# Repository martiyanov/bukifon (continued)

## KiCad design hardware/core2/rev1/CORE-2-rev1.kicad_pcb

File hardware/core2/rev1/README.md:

# CORE-2 rev.1 — PCB scaffold (PRE-FREEZE)

> **Не заказывать PCB.** Это каркас разводки из `mechanical/board-fit/`: контур, крепёж,
> keepout-зоны и стек. Нет посадочных мест компонентов (кроме крепежа), нет netlist/связей,
> нет меди/трасс. Следующий шаг — импорт схемы CORE-2 rev.3 (netlist) и посадочных мест.

## Что есть

| Файл | Что |
|---|---|
| `CORE-2-rev1.kicad_pcb` | плата: Edge.Cuts 200×108 мм, 4×M3 (Ø3.4, H1–H4), keepout-зоны, стек 6 слоёв 1.6 мм |
| `CORE-2-rev1.svg/.pdf` | контур + шелкография (для проверки/обсуждения) |
| `CORE-2-rev1.drc.rpt` | `kicad-cli pcb drc --severity-all`: **0 нарушений, 0 unconnected** |
| `gen_scaffold.py` | генератор из `mechanical/board-fit/board-spec.json` (общий для CORE/PANEL/PWR) |
| `verify_scaffold.py` | сверка координат с board-spec, допуск **±0.05 мм** — **PASS** |

## Параметры

- Контур: прямоугольник 200×108 мм (origin world 90;51), площадь 21 600 мм².
- Крепёж: 4×M3 Ø3.4 (NPTH, стойка Ø7) — H1 (5;8), H2 (195;8), H3 (5;100), H4 (195;100) в локальных мм.
- Стек: 6 меди (F.Cu / In1–In4 / B.Cu), FR4, 1.6 мм; толщина меди 0.035 мм (1 oz), диэлектрик распределён.
- Keepout (только медь/трассы/via, NPTH-пады разрешены): `C6-antenna` 40×20 + правило ≥15 мм,
  `analog` (DAC/ADC, звезда GND), `DC-DC` (тепловой/горячий контур).
  `USB-C` keepout из board-spec лежит вне контура платы (окно в задней стенке корпуса) — в плату не переносится.

## Проверки

- **DRC**: 0 errors / 0 warnings / 0 unconnected (`CORE-2-rev1.drc.rpt`).
- **Сверка с board-spec**: PASS (±0.05 мм): контур, 4 отверстия, толщина 1.6, 6 Cu, keepout-зоны.
- Импорт DXF (`mechanical/board-fit/core2.dxf`) в KiCad: File→Import→DXF→Edge.Cuts —
  альтернатива; текстовые сегменты сгенерированы точно по `board-spec.json` (DXF-круги
  крепежа заменены NPTH-падами, как требует DFM).

## Что дальше

1. Импорт netlist CORE-2 rev.3 (`hardware/core2/CORE-2.kicad_sch` → Update PCB) после снятия PRE-FREEZE.
2. Посадочные места (модуль P4, C6, FPC-40, IDC, аудио/джеки, TP-пады) + правила DRC.
3. Медная заливка/GND-полигоны, стек-ап импедансов (USB HS 90 Ω), keepout-механика (антенна vs H1).
4. DFM-ревью `hardware/core2/dfm.md` + `docs/38`, затем заказ прототипов 3–5 шт.

## Нетлист и посадочные места — первый импорт (2026-11-06)

- Источник: `hardware/core2/netlist.xml` (CORE-2 rev.3) + `BOM-core2.csv` (footprint по позициям).
- **Refs: 373/373** на плате; 4 NPTH-крепления (H1–H4) — из каркаса.
- **Footprints: 373** (имена из BOM; в PCB — bare-имена и упрощённые пады 0.5×0.8/шаг 1.0 с
  корректными номерами/числом; реальные `.kicad_mod` подтянуть при разводке). Pads: **1224**.
- **Placeholder: 16** — требуют реальных футпринтов до трассировки:
  `A1` (P4-модуль/адаптер), `U31` (C6-MINI-1), `U22` (BQ24074), `U26` (MP1584),
  `J6/J7/J8/J9/J10` (TRS/3.5 джеки), `J11` (audio jack), `J12` (DC jack), `J13` (mic TRS),
  `J20` (mic TRS), `SW1/SW2/SW3` (кнопки/тумблер).
- Зоны: `J1` USB-C у задней кромки, `U31` C6 — рядом с антенной (вне keepout), `A1` — центр;
  остальное — сетка по секциям (DC-DC/аналог — при ручной разводке).
- **DRC: 0 errors / 0 warnings; unconnected (неразведённые) = 499** — допустимо на этом этапе.
- Перегенерация: `python gen_scaffold.py && python import_netlist.py && python verify_import.py`
  (из корня репозитория пути уже учтены; скрипты лежат в `hardware/core2/rev1/`).
- Дальше: заменить 16 placeholder на реальные посадочные места, затем трассировка — после MCU freeze.

## Реальные футпринты и DRC-правила (2026-11-06)

- **Placeholder'ы заменены полностью (0):** A1 — custom `A1_P4_MODULE_ADAPTER` (2×32, шаг 2.54,
  габарит адаптера 90×28), U31 — custom `C6_MINI_1` (13.2×16.6), U26 — custom `MP1584_MODULE`
  (4 пада), U22 — `Package_DFN_QFN:QFN-16-1EP_3x3mm_P0.5mm_EP1.75x1.75mm`, J6–J11/J13/J20 —
  `Connector_Audio:Jack_3.5mm_CUI_SJ1-3535NG_Horizontal`, J12 — `Connector_BarrelJack:BarrelJack_CUI_PJ-063AH_Horizontal`,
  SW1–SW3 — `Button_Switch_THT:SW_PUSH_6mm`. Кастомные `.kicad_mod` — в `footprints/`
  (+`fp-lib-table`), вставлены через **pcbnew Python API** (реальная геометрия, пады с net).
- **Стандартные пассивные/IC**: footprint-имена из BOM (KiCad-библиотеки); в каркасе пады
  упрощённые (0.5×0.8/шаг 1.0) — полные `.kicad_mod` подтягиваются при разводке
  (`import_netlist.py`: generic-пады; `add_real_footprints.py`: реальные для заменённых).
- **Footprints: 373** (+4 NPTH), pads **1259**; refs 373/373; **DRC 0 errors / 0 warnings**,
  unconnected 499 (неразведённые).
- **DRC-правила/классы** (`CORE-2-rev1.kicad_pro`): `Default`, `Power` (+12/−12/5/3.3/VSYS…,
  ширина 1.0 мм), `USB_HS` (90 Ω: diff 0.2/0.2, clearance 0.15), `Audio` (0.25 мм),
  `RF` (C6 SPI); track widths 0.2–2.0, via 0.6/0.3 и 0.8/0.45, diff pair 0.2/0.2;
  правила-исключения для каркаса (silk/courtyard) — в `rule_severities`.
- **GND-полигоны (план, без заливки):** F.Cu/B.Cu GND-заливка после трассировки; аналоговая
  зона (DAC/ADC) — отдельный AGND-полигон, звезда в NT1/NT2; PGND — силовая зона, соединение
  в одной точке у J17; под антенной C6 — запрет меди (keepout 40×20 + ≥15 мм). Заливку делать
  только после MCU freeze/трассировки.

## Статус: реальные пассивы/GND-полигоны (2026-11-06)

- Placeholder'ы: **0** (A1/C6/MP1584/CHOC/джеки/кнопки/QFN — реальные).
- Стандартные пассивы: остаются **упрощёнными падами 0.5×0.8 (328)**; footprint-имена из BOM
  назначены. Полный перевод (`build_full_pcb.py`, реальные `.kicad_mod` для всех) пока **не прошёл
  DRC**: крупные реальные футпринты не упаковываются без пересечений на 200×108 — требуется
  трассировка/оптимизация размещения после MCU freeze.
- GND/AGND/PGND-полигоны: **не залиты** (план в docs/82 §11; `add_gnd_zones.py` даёт
  `isolated_copper`/`zones_intersect`/`starved_thermal`) — следующий шаг вместе с трассировкой.
- Текущий DRC: **0 errors / 0 warnings**; `verify_import.py` PASS (+счётчик `SIMPLIFIED PADS: 328`).

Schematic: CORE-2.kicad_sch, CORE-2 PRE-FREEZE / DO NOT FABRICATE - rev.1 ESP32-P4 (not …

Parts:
A1: ESP32-P4NRW32 + 32MB PSRAM (module TBD)
C1, C4, C6, C17, C20, C32, C41, C48, C49, C57, C63, C82, C84, C94: 10uF/10V; C_0805_2012Metric
C2: 100nF/16V; C_0805_2012Metric
C3, C5, C7, C19, C21, C22, C26, C37, C42, C43, C44, C45, C46, C47, C51, C54, C55, C56, C60, C61, C62, C64, C65, C68, C69, C73, C75, C76, C81, C83, C85, C86, C87, C88, C89, C90, C91, C92, C93, C95, C96, C97, C98, C101, C102, C103, C115, C116, C118, C119, C120, C121, C127, C129: 100nF; C_0805_2012Metric
C8, C16, C99, C100: 100nF; C_0805_2012Metric; not fitted
C9, C13: 100pF; C_0805_2012Metric; not fitted
C10, C14: 10uF/10V; C_0805_2012Metric; not fitted
C11, C28: 220uF/25V; CP_Elec_6.3x7.7; not fitted
C12, C29: 100nF/50V; C_0805_2012Metric; not fitted
C15: 220uF/10V; CP_Elec_6.3x7.7; not fitted
C18, C40, C114, C117: 100uF/10V; CP_Elec_6.3x7.7
C24, C25, C35: 1uF; C_0805_2012Metric
C27: 1.5nF; C_0805_2012Metric; not fitted
C30: 100uF/25V; CP_Elec_6.3x7.7; not fitted
C31, C70, C71, C77, C79: 100pF; C_0805_2012Metric
C33: 10uF/35V; C_0805_2012Metric
C34, C104, C106, C107, C109, C111, C113: 100nF/50V; C_0805_2012Metric
C36, C53: 22uF/10V; C_0805_2012Metric
C38, C110, C112: 100uF/25V; CP_Elec_6.3x7.7
C39: 220uF/25V; CP_Elec_6.3x7.7
C58, C122: 1uF/10V; C_0805_2012Metric
C59: 1uF/10V; CP_Elec_6.3x7.7
C66, C67: 10uF/16V; CP_Elec_6.3x7.7
C72, C74, C128: 10uF/10V; CP_Elec_6.3x7.7
C78, C80, C126: 1uF/16V; C_0805_2012Metric
C105, C108: 10uF/25V; CP_Elec_6.3x7.7
C123, C125: 470nF; C_0805_2012Metric
C124: 2.2uF/10V; C_0805_2012Metric
D1, D30: SMAJ5.0A; D_SMA
D2, D7, D18, D19, D21, D22, D28: SS34; D_SMA
D3: CHG; C_0805_2012Metric
D4, D5, D6: SS34; D_SMA; not fitted
D8, D9, D10, D11, D12, D13, D14, D15, D16, D17, D24, D25: BAT54S; SOT-23
D20, D23, D29: SMAJ15A; D_SMA
D31: MIC ON; C_0805_2012Metric
F1: 1.5A; Fuse_1206_3216Metric
F2, F4: 0.5A; Fuse_1206_3216Metric
F3, F5: 0.3A; Fuse_1206_3216Metric
FB1, FB2, FB3, FB4, FB5, FB6, FB7, FB8: 600R@100MHz; L_0805_2012Metric
J1: USB-C 16P (data+charge); USB_C_Receptacle_HRO_TYPE-C-31-M-12
J2: BATTERY 1S2P; JST_XH_B2B-XH-A_1x02_P2.50mm_Vertical; not fitted
J4: UART0 TP; PinHeader_1x03_P2.54mm_Vertical
J5: microSD (SDIO 1-bit); microSD_HC_Hirose_DM3AT-SF-PEJM5
J6: MIDI IN TRS-A
J7: MIDI OUT TRS-A
J8: LINE OUT L/R 3.5mm
J9: PHONES 3.5mm
J10: AUDIO IN L 3.5mm
J11: AUDIO IN R 3.5mm
J12: DC 12V 5.5/2.1
J13: EXPRESSION TRS; not fitted
J14: PANEL-2 J14 (IDC-26) analog field [rev.2 canon]; IDC-Header_2x13_P2.54mm_Latch12.0mm_Vertical
J15: PANEL-2 J12 (FFC-40) LCD RGB565+BL [rev.2 canon]; Hirose_FH12-40S-0.5SH_1x40-1MP_P0.50mm_Horizontal
J16: PANEL-2 J13 (IDC-16) digital/power [rev.2 canon]; IDC-Header_2x08_P2.54mm_Latch6.5mm_Vertical
J17: PWR-2 J3 (IDC-20) [rev.2]; IDC-Header_2x10_P2.54mm_Vertical
J18: PWR-2 J4 (IDC-12) [rev.2]; IDC-Header_2x06_P2.54mm_Vertical
J19: PANEL-2 MEMS mic (IDC-6); IDC-Header_2x03_P2.54mm_Vertical
J20: MIC IN 3.5mm TRS (electret)
L1, L2: 22uH; L_1210_3225Metric; not fitted
L3: 220uH; L_1210_3225Metric; not fitted
L4: 22uH; L_1210_3225Metric
NT1: AGND=DGND; NetTie-2_SMD_Pad0.5mm
NT2: DGND=PGND; NetTie-2_SMD_Pad0.5mm
P1: PicoMod analog bus IDC-26 PORT1; IDC-Header_2x13_P2.54mm_Latch12.0mm_Vertical
P2: PicoMod analog bus IDC-26 PORT2; IDC-Header_2x13_P2.54mm_Latch12.0mm_Vertical
Q1, Q2: AO3400A; SOT-23; not fitted
Q3, Q4, Q5: 2N7000; TO-92_Inline
R1, R2: 1.5k; R_0805_2012Metric
R3: 2k; R_0805_2012Metric
R4, R19, R20, R37, R38, R63, R65, R75, R85, R88, R92, R93, R99, R100, R108, R110, R113: 100k; R_0805_2012Metric
R5, R14: 10k; R_0805_2012Metric; not fitted
R6, R43, R44, R57, R58, R59, R60, R61, R62, R67, R68, R71, R72, R84, R87, R103, R104, R114: 1k; R_0805_2012Metric
R7, R90: 330; R_0805_2012Metric; not fitted
R10: 91k; R_0805_2012Metric; not fitted
R11: 4.7k; R_0805_2012Metric; not fitted
R12, R15: 100k; R_0805_2012Metric; not fitted
R13: 75k; R_0805_2012Metric; not fitted
R16: 0.33; R_0805_2012Metric; not fitted
R17: 33k; R_0805_2012Metric; not fitted
R18: 3.9k; R_0805_2012Metric; not fitted
R21: 3.09k; R_0805_2012Metric
R22, R23, R24, R27, R30, R31, R35, R36, R51, R52, R53, R54, R55, R56, R77, R91: 10k; R_0805_2012Metric
R28, R29: 5.1k; R_0805_2012Metric
R39, R40, R41, R42: 100; R_0805_2012Metric
R45, R46, R47, R48, R49, R50: 39k; R_0805_2012Metric
R64, R66, R101, R102: 16.5k; R_0805_2012Metric
R69, R70, R76: 47k; R_0805_2012Metric
R73, R74: 1k; R_0805_2012Metric; not fitted
R78, R79, R106: 2.2k; R_0805_2012Metric
R80, R83: 220; R_0805_2012Metric
R81, R86, R89: 4.7k; R_0805_2012Metric
R82: 33; R_0805_2012Metric
R94, R95, R96, R97, R98, R105: 0R; R_0805_2012Metric
R107: 150k; R_0805_2012Metric
SW1: BOOT
SW2: RESET
SW3: MIC MUTE
TB1: Rear audio terminal block; TerminalBlock_Phoenix_MKDS-1-12-3.81_1x12_P3.81mm_Horizontal
TB2: Rear MIDI/DC/EXPR terminal block; TerminalBlock_Phoenix_MKDS-1-10-3.81_1x10_P3.81mm_Horizontal; not fitted
TH1: NTC 10k; R_0805_2012Metric; not fitted
TH2: NTC 10k; R_0805_2012Metric
TP1: VBUS_CHG; TestPoint_Pad_D1.5mm
TP2: VSYS; TestPoint_Pad_D1.5mm
TP3: 12V; TestPoint_Pad_D1.5mm
TP4: -12V; TestPoint_Pad_D1.5mm
TP5: 5V; TestPoint_Pad_D1.5mm
TP6: 3V3; TestPoint_Pad_D1.5mm
TP7: 3V3_MCU; TestPoint_Pad_D1.5mm
TP8: BATT_MON; TestPoint_Pad_D1.5mm
TP9: I2S_MCLK; TestPoint_Pad_D1.5mm
TP10: SD_CLK; TestPoint_Pad_D1.5mm
TP11: USB_HS_DP; TestPoint_Pad_D1.5mm
TP12: USB_HS_DM; TestPoint_Pad_D1.5mm
TP13: AGND; TestPoint_Pad_D1.5mm
TP14: DGND; TestPoint_Pad_D1.5mm
TP15: PGND; TestPoint_Pad_D1.5mm
TP16: LED_DATA; TestPoint_Pad_D1.5mm
TP17: CHIP_PU; TestPoint_Pad_D1.5mm
TP18: BOOT; TestPoint_Pad_D1.5mm
TP19: 3V3_C6; TestPoint_Pad_D1.5mm
TP20: BL_20V; TestPoint_Pad_D1.5mm
TP21: C6_CS; TestPoint_Pad_D1.5mm
TP22: C6_RST; TestPoint_Pad_D1.5mm
TP23: N12_EXT; TestPoint_Pad_D1.5mm
TP24: 5V_EXT; TestPoint_Pad_D1.5mm
TP25: 5V_LED; TestPoint_Pad_D1.5mm
TP26: PWR_GOOD; TestPoint_Pad_D1.5mm
TP27: EN_RAILS; TestPoint_Pad_D1.5mm
TP28: LED_RET; TestPoint_Pad_D1.5mm
TP29: I2S_BCK; TestPoint_Pad_D1.5mm
TP30: I2S_LRCK; TestPoint_Pad_D1.5mm
TP31: MIC_DATA; TestPoint_Pad_D1.5mm
TP32: MIC_BCK; TestPoint_Pad_D1.5mm
U20, U48, U49: USBLC6-2SC6; SOT-23-6
U22: BQ24074RGT
U23: BQ29700DSER; SOT-23-6; not fitted
U24: MT3608 (+12V); SOT-23-6; not fitted
U25: MT3608 (+5V); SOT-23-6; not fitted
U26: MP1584 3.3V/3A (MCU)
U27: AP2112K-3.3; SOT-23-5
U28: MC34063; DIP-8_W7.62mm; not fitted
U29: MT3608 (+20V BL); SOT-23-6
U30: AP2112K-3.3 (C6); SOT-23-5
U31: ESP32-C6-MINI-1 (Wi-Fi6/BLE5.3)
U32: PCM5102A; TSSOP-20_4.4x6.5mm_P0.65mm
U33: TL072; DIP-8_W7.62mm
U34: PCM1808PWR; TSSOP-14_4.4x5mm_P0.65mm
U35: MCP4728A0-E/UN (0x60); MSOP-10_3x3mm_P0.5mm
U36: MCP4728A1-E/UN (0x61); MSOP-10_3x3mm_P0.5mm
U37, U38, U39, U45: TL074; DIP-14_W7.62mm
U40: MCP3208; DIP-16_W7.62mm
U41: 24LC32A; DIP-8_W7.62mm
U42: 6N137; DIP-8_W7.62mm
U43: 74HCT125; SOIC-14_3.9x8.7mm_P1.27mm
U44: 74HCT1G125; SOT-353_SC-70-5; not fitted
U46: MAX9814 (AGC mic amp); TDFN-14-1EP_3x3mm_P0.4mm_EP1.78x2.35mm
U47: TS5A23157 (line/mic switch); MSOP-10-1EP_3x3mm_P0.5mm_EP1.68x1.88mm

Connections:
3V3: C25.1, C26.1, C56.1, C57.1, C61.1, C62.1, C63.1, C64.1, C76.1, C81.1, C82.1, C83.1, C84.1, C96.1, C103.1, D16.2 (K), D17.2 (K), D24.2 (K), D25.2 (K), FB5.1, FB6.1, FB8.1, J5.4 (VDD), J13.R, R30.1, R31.1, R35.1, R36.1, R69.1, R78.1, R79.1, R81.1, R91.1, R92.1, R93.1, R105.2, TB2.10, TH2.1, TP6.1, U27.5 (VOUT), U32.1 (CPVDD), U32.8 (AVDD), U32.20 (DVDD), U34.4 (VDD), U35.1 (VDD), U36.1 (VDD), U40.16 (Vdd), U41.1 (A0), U41.2 (A1), U41.3 (A2), U41.8 (VCC), U47.8 (VCC), U48.5 (VBUS), U49.5 (VBUS)
3V3_C6: C36.1, C37.1, C53.1, C54.1, C55.1, R27.1, TP19.1, U30.5 (VOUT), U31.1 (3V3)
3V3_MCU: A1.3 (3V3), A1.4 (3V3), C20.1, C21.1, C22.1, C42.1, C43.1, C44.1, C45.1, C46.1, C47.1, C48.1, C49.1, FB1.2, R22.1, R23.1, R24.2, TP7.1
3V3_MCU_RAW: C18.1, C19.1, FB1.1, U26.3 (OUT+)
3V3_MIC: C128.1, C129.1, FB8.2, J19.6, R113.1, R114.1, U46.5 (VDD)
3V3_PANEL: C41.1, FB5.2, J15.27, J15.28, J16.11
5V: C13.1, C15.1, C16.1, C17.1, C24.1, C32.1, C35.1, C74.1, C75.1, C117.1, D5.2 (A), D8.2 (K), D9.2 (K), FB4.1, FB7.2, L4.1, R13.1, R19.1, R83.1, R86.1, R89.1, TP5.1, U26.1 (IN+), U27.1 (VIN), U27.3 (EN), U29.5 (IN), U30.1 (VIN), U30.3 (EN), U34.3 (VCC), U42.7 (EN), U42.8 (VCC), U43.4 (2OE), U43.10 (3OE), U43.13 (4OE), U43.14 (VCC), U44.5 (VCC)
5V_EXT: C114.1, C115.1, FB7.1, J17.13, J17.14, TP24.1
5V_LED: C116.1, J16.9, J16.13, J17.17, TP25.1
5V_PANEL: C40.1, FB4.2
12V: C9.1, C11.1, C12.1, C29.1, C30.1, C68.1, C85.1, C87.1, C92.1, C120.1, D2.2 (A), D4.2 (A), D10.2 (K), D11.2 (K), D12.2 (K), D13.2 (K), D14.2 (K), D15.2 (K), FB2.1, R10.1, R16.1, TP3.1, U28.6 (Vin), U33.8 (V+), U37.4 (V+), U38.4 (V+), U39.4 (V+), U45.4 (V+)
12V_B: C38.1, D18.2 (A), D21.2 (A), F2.1, F4.1, FB2.2
12V_EXT: C110.1, C111.1, D2.1 (K), J12.1, J17.5, J17.6, TB2.7
12V_P1: C104.1, C105.1, D18.1 (K), D29.1 (A1), F2.2, P1.1
12V_P2: C107.1, C108.1, D21.1 (K), D23.1 (A1), F4.2, P2.1
-12V: C27.2, C28.2, C29.2, C69.1, C86.1, C88.1, C93.1, C121.1, D19.1 (K), FB3.1, L3.2, R18.2, TP4.1, U28.4 (GND), U33.4 (V-), U37.11 (V-), U38.11 (V-), U39.11 (V-), U45.11 (V-)
-12V_B: C39.2, D22.1 (K), D28.1 (K), F3.1, F5.1, FB3.2
AGND: C59.1, C60.2, C61.2, C63.2, C64.2, C65.2, C68.2, C69.2, C70.2, C71.2, C72.2, C73.2, C74.2, C75.2, C77.2, C79.2, C81.2, C82.2, C83.2, C84.2, C85.2, C86.2, C87.2, C88.2, C89.2, C90.2, C91.2, C92.2, C93.2, C94.2, C95.2, C96.2, C97.2, C98.2, C99.2, C100.2, C101.2, C102.2, C118.2, C119.2, C120.2, C121.2, C122.2, C123.2, C124.2, C125.2, C128.2, C129.2, D8.1 (A), D9.1 (A), D10.1 (A), D11.1 (A), D12.1 (A), D13.1 (A), D14.1 (A), D15.1 (A), D16.1 (A), D17.1 (A), D24.1 (A), D25.1 (A), D30.2 (A2), J8.S, J9.S, J10.S, J11.S, J13.S, J14.2, J14.4, J14.6, J14.8, J14.10, J14.12, J14.14, J14.16, J14.18, J14.20, J14.22, J14.24, J14.26, J20.S, NT1.1, P1.6, P1.8, P1.10, P1.12, P1.18, P1.20, P1.22, P1.24, P2.6, P2.8, P2.10, P2.12, P2.18, P2.20, P2.22, P2.24, Q5.3 (S), R37.2, R38.2, R51.2, R52.2, R53.2, R54.2, R55.2, R56.2, R70.2, R74.2, R76.2, R77.2, R108.2, R110.2, SW3.2 (B), TB1.3, TB1.6, TB1.9, TB1.10, TB1.11, TB1.12, TP13.1, U32.3 (CPGND), U32.9 (AGND), U34.2 (AGND), U35.10 (VSS), U36.10 (VSS), U38.10 (+), U38.12 (+), U39.12 (+), U40.14 (AGND), U45.10 (+), U45.12 (+), U46.4 (NC4), U46.7 (GND), U46.9 (AR), U46.10 (GAIN), U46.11 (NC11), U46.15 (EP), U47.3 (GND)
AUDIN_L: J10.T, P1.17, P2.17, R43.1, TB1.7
AUDIN_L_C: C78.2, U34.13 (VINL)
AUDIN_L_F: C77.1, D8.3 (COM), R43.2, U47.9 (NC1)
AUDIN_R: J11.T, P1.19, P2.19, R44.1, TB1.8
AUDIN_R_C: C80.2, U34.14 (VINR)
AUDIN_R_F: C79.1, D9.3 (COM), R44.2, U47.7 (NC2)
AUDL_BUF: R39.1, R41.1, U33.1, U33.2 (-)
AUDOUT_L: C70.1, J8.T, P1.21, P2.21, R39.2, TB1.1
AUDOUT_R: C71.1, J8.R, P1.23, P2.23, R40.2, TB1.2
AUDR_BUF: R40.1, R42.1, U33.6 (-), U33.7
AUD_L_IN: C66.2, R37.1, U33.3 (+)
AUD_R_IN: C67.2, R38.1, U33.5 (+)
BATT_MON: C101.1, R75.2, R76.1, TP8.1, U40.7 (CH6)
BATT_MON_RAW: J18.1, R75.1
BATT_N: C8.2, J2.2, Q1.3 (S), U23.4 (VSS)
BATT_P: C6.1, C7.1, J2.1, J17.3, J17.4, R7.1, U22.2 (BAT), U22.3 (BAT)
BIAS: C123.1, U46.12 (BIAS)
BL_20V: C31.1, C33.1, C34.1, D7.2 (A), J15.31, R20.1, TP20.1
BL_CATHODE: J15.32, R97.1
BL_PWM: A1.16 (IO49), J15.30
BMS_MID: Q1.2 (D), Q2.2 (D)
BOOT: A1.8 (IO35), R22.2, SW1.1, TP18.1
BQ_BAT: C8.1, R7.2, U23.5 (BAT)
C6_CS: A1.10 (IO26), TP21.1, U31.7 (SPI_CS)
C6_DR: A1.12 (IO25), U31.9 (DATA_READY)
C6_HS: A1.11 (IO24), U31.8 (HANDSHAKE)
C6_RST: A1.13 (IO27), R27.2, TP22.1, U31.3 (EN)
CC1: J1.A5 (CC1), R28.1
CC2: J1.B5 (CC2), R29.1
CG: C124.1, U46.3 (CG)
CHG: D3.1 (K), U22.9 (~CHG)
CHG_LED: D3.2 (A), R6.2
CHIP_PU: A1.5 (EN), C51.1, R23.2, SW2.1, TP17.1
CP_M: C58.2, U32.4 (CAPM)
CP_P: C58.1, U32.2 (CAPP)
CT: C125.1, U46.1 (CT)
CVIN1: J14.9, R63.1
CVIN1_ADC: C89.1, D16.3 (COM), R67.2, U40.1 (CH0)
CVIN1_N: R63.2, R64.1, U39.2 (-)
CVIN1_RAW: R64.2, R67.1, U39.1
CVIN2: J14.11, R65.1
CVIN2_ADC: C90.1, D17.3 (COM), R68.2, U40.2 (CH1)
CVIN2_N: R65.2, R66.1, U39.6 (-)
CVIN2_RAW: R66.2, R68.1, U39.7
CVIN3: J14.13, R99.1
CVIN3_ADC: C118.1, D24.3 (COM), R103.2, U40.5 (CH4)
CVIN3_N: R99.2, R101.1, U45.2 (-)
CVIN3_RAW: R101.2, R103.1, U45.1
CVIN4: J14.15, R100.1
CVIN4_ADC: C119.1, D25.3 (COM), R104.2, U40.6 (CH5)
CVIN4_N: R100.2, R102.1, U45.6 (-)
CVIN4_RAW: R102.2, R104.1, U45.7
CVOUT1: D10.3 (COM), J14.1, P1.5, P2.5, R57.2
CVOUT2: D11.3 (COM), J14.3, P1.7, P2.7, R58.2
CVOUT3: D12.3 (COM), J14.5, P1.9, P2.9, R59.2
CVOUT4: D13.3 (COM), J14.7, P1.11, P2.11, R60.2
CVOUT5: D14.3 (COM), R61.2
CVOUT6: D15.3 (COM), R62.2
CVR0: R45.2, R57.1, U37.1
CVR1: R46.2, R58.1, U37.7
CVR2: R47.2, R59.1, U37.8
CVR3: R48.2, R60.1, U37.14
CVR4: R49.2, R61.1, U38.1
CVR5: R50.2, R62.1, U38.7
CVREF: C91.1, R69.2, R70.1, U39.10 (+)
CVREF_B: U39.3 (+), U39.5 (+), U39.8, U39.9 (-), U45.3 (+), U45.5 (+)
CVS0: R45.1, R51.1, U37.2 (-)
CVS1: R46.1, R52.1, U37.6 (-)
CVS2: R47.1, R53.1, U37.9 (-)
CVS3: R48.1, R54.1, U37.13 (-)
CVS4: R49.1, R55.1, U38.2 (-)
CVS5: R50.1, R56.1, U38.6 (-)
DAC_A: U35.6 (VOUTA), U37.3 (+)
DAC_B: U35.7 (VOUTB), U37.5 (+)
DAC_C: U35.8 (VOUTC), U37.10 (+)
DAC_D: U35.9 (VOUTD), U37.12 (+)
DAC_E: U36.6 (VOUTA), U38.3 (+)
DAC_F: U36.7 (VOUTB), U38.5 (+)
DAC_L: C66.1, U32.6 (OUTL)
DAC_R: C67.1, U32.7 (OUTR)
DGND: A1.1 (GND), A1.2 (GND), A1.63 (GND), A1.64 (GND), C20.2, C21.2, C22.2, C24.2, C25.2, C26.2, C35.2, C36.2, C37.2, C41.2, C42.2, C43.2, C44.2, C45.2, C46.2, C47.2, C48.2, C49.2, C51.2, C53.2, C54.2, C55.2, C56.2, C57.2, C62.2, C76.2, C103.2, J1.A1 (GND), J1.A12 (GND), J1.B1 (GND), J1.B12 (GND), J1.SH (SHIELD), J4.1, J5.6 (VSS), J5.SH (SHIELD), J6.S, J7.S, J15.1, J15.2, J15.19, J15.20, J15.25, J15.26, J15.29, J15.33, J15.34, J15.35, J15.36, J15.37, J15.38, J15.39, J15.40, J16.2, J16.4, J16.6, J16.8, J16.10, J16.12, J16.14, J19.2, J19.4, NT1.2, NT2.1, P1.14, P1.16, P2.14, P2.16, Q3.1 (S), Q4.1 (S), R28.2, R29.2, R85.2, R88.2, SW1.2, SW2.2, TB2.3, TB2.6, TP14.1, U20.2 (GND), U27.2 (GND), U30.2 (GND), U31.2 (GND), U31.10 (GND), U32.10 (DEMP), U32.11 (FLT), U32.16 (FMT), U32.19 (DGND), U34.5 (DGND), U34.10 (MD0), U34.11 (MD1), U34.12 (FMT), U35.4 (~LDAC), U36.4 (~LDAC), U40.9 (DGND), U41.4 (GND), U41.7 (WP), U42.5 (GND), U43.1 (1OE), U43.5 (2A), U43.7 (GND), U43.9 (3A), U43.12 (4A), U44.1 (~OE), U44.3 (GND), U48.2 (GND), U49.2 (GND)
EN5: R15.2, U25.4 (EN)
EN12: R12.2, U24.4 (EN)
ENBL: R19.2, U29.4 (EN)
EN_5V: J18.10, R96.2
EN_BUS12: J18.7, R94.2
EN_LED5: J14.25, J18.9
EN_N12: J18.8, R95.2
EN_RAILS: J16.15, R94.1, R95.1, R96.1, TP27.1
EXPR: J13.T, R73.1, TB2.9
EXPR_ADC: C99.1, R73.2
FADER1: J14.21, R71.1
FADER1_ADC: C97.1, R71.2, U40.3 (CH2)
FADER2: J14.23, R72.1
FADER2_ADC: C98.1, R72.2, U40.4 (CH3)
FB5: C13.2, R13.2, R14.1, U25.3 (FB)
FB12: C9.2, R10.2, R11.1, U24.3 (FB)
FBBL: C31.2, R20.2, R21.1, U29.3 (FB)
FUEL_ALRT: J18.5, R93.2
G1: Q3.2 (G), R84.2, R85.1
G2: Q4.2 (G), R87.2, R88.1
GATE1: J14.17, P1.13, P2.13, Q3.3 (D), R86.2
GATE1_GPIO: A1.19 (IO52), R84.1
GATE2: P1.15, P2.15, Q4.3 (D), R89.2
GATE2_GPIO: A1.20 (IO53), R87.1
G_BMS_C: Q1.1 (G), U23.2 (Cout)
G_BMS_D: Q2.1 (G), U23.3 (Dout)
I2C0_SCL: A1.36 (IO22), J16.3, J18.4, R79.2, U35.2 (SCL), U36.2 (SCL), U41.6 (SCL)
I2C0_SDA: A1.35 (IO21), J16.1, J18.3, R78.2, U35.3 (SDA), U36.3 (SDA), U41.5 (SDA)
I2S_ADC_DOUT: A1.34 (IO19), U34.9 (DOUT)
I2S_BCK: A1.31 (IO16), TP29.1, U32.13 (BCK), U34.8 (BCK)
I2S_DAC_DIN: A1.33 (IO18), U32.14 (DIN)
I2S_LRCK: A1.32 (IO17), TP30.1, U32.15 (LRCK), U34.7 (LRCK)
I2S_MCLK: A1.30 (IO20), TP9.1, U32.12 (SCK), U34.6 (SCKI)
ILIM: R1.1, U22.12 (ILIM)
ISET: R2.1, U22.16 (ISET)
ITERM: R3.1, U22.15 (ITERM)
LCD_B0: A1.47 (IO0), J15.14
LCD_B1: A1.48 (IO1), J15.15
LCD_B2: A1.49 (IO2), J15.16
LCD_B3: A1.50 (IO3), J15.17
LCD_B4: A1.51 (IO4), J15.18
LCD_DE: A1.44 (IO13), J15.22
LCD_DISP: A1.17 (IO50), R105.1
LCD_G0: A1.52 (IO5), J15.8
LCD_G1: A1.53 (IO23), J15.9
LCD_G2: A1.54 (IO28), J15.10
LCD_G3: A1.55 (IO29), J15.11
LCD_G4: A1.56 (IO30), J15.12
LCD_G5: A1.57 (IO31), J15.13
LCD_HSYNC: A1.45 (IO14), J15.23
LCD_PCLK: A1.43 (IO12), J15.21
LCD_R0: A1.58 (IO32), J15.3
LCD_R1: A1.59 (IO33), J15.4
LCD_R2: A1.60 (IO34), J15.5
LCD_R3: A1.61 (IO46), J15.6
LCD_R4: A1.62 (IO47), J15.7
LCD_VSYNC: A1.46 (IO15), J15.24
LDOO: C60.1, U32.18 (LDOO)
LED_5V: R90.1, U44.4 (Y)
LED_DATA: J16.7, R90.2, R98.2, TP16.1
LED_GPIO: A1.15 (IO48), R98.1, U44.2 (A)
LED_RET: J16.16, J17.18, TP28.1
MCP3208_CS: A1.40 (IO9), U40.10 (~CS/SHDN)
MC_A: R16.2, U28.1 (SwC), U28.7 (Ipk), U28.8 (DC)
MC_FB: R17.2, R18.1, U28.5 (Vfb)
MC_SW: D6.1 (K), L3.1, U28.2 (SwE)
MC_TC: C27.1, U28.3 (TC)
MICBIAS_N: C122.1, R106.1, R107.1, U46.13 (MCBIAS)
MICIN_A: C127.2, U46.8 (MICIN)
MIC_AGC: C126.1, U46.6 (MICOUT)
MIC_BCK: A1.24 (IO40), J19.1, TP32.1, U48.1 (I/O1), U48.6 (I/O1)
MIC_BIAS: J20.R, R106.2
MIC_DATA: A1.26 (IO42), J19.5, TP31.1, U49.1 (I/O1), U49.6 (I/O1)
MIC_IN: C127.1, D30.1 (A1), J20.T
MIC_LED_A: D31.2 (A), R114.2
MIC_LED_K: D31.1 (K), Q5.2 (D)
MIC_SEL: A1.14 (IO54), R110.1, U47.1 (IN1), U47.5 (IN2)
MIC_WS: A1.25 (IO41), J19.3, U48.3 (I/O2), U48.4 (I/O2)
MIDI_A: R80.2, U42.2 (A)
MIDI_DRV: R82.1, U43.3 (1Y)
MIDI_IN_R: J6.R, R80.1, TB2.2
MIDI_IN_T: J6.T, TB2.1, U42.3 (C)
MIDI_OUT_R: J7.R, R83.2, TB2.5
MIDI_OUT_T: J7.T, R82.2, TB2.4
MIDI_RX: A1.42 (IO11), R81.2, U42.6 (VO)
MIDI_TX: A1.41 (IO10), U43.2 (1A)
N12V_P1: C106.1, D28.2 (A), F3.2, P1.3
N12V_P2: C109.1, D22.2 (A), F5.2, P2.3
N12_EXT: C112.1, C113.1, D19.2 (A), D20.1 (A1), J17.9, J17.10, TP23.1
NTC_PACK: C3.1, J18.2, U22.1 (TS)
PANEL_IRQ: A1.18 (IO51), J16.5, R91.2
PGND: C1.2, C2.2, C3.2, C4.2, C5.2, C6.2, C7.2, C10.2, C11.2, C12.2, C14.2, C15.2, C16.2, C17.2, C18.2, C19.2, C28.1, C30.2, C32.2, C33.2, C34.2, C38.2, C39.1, C40.2, C104.2, C105.2, C106.2, C107.2, C108.2, C109.2, C110.2, C111.2, C112.2, C113.2, C114.2, C115.2, C116.2, C117.2, D1.2 (A2), D6.2 (A), D20.2 (A2), D23.2 (A2), D29.2 (A2), J12.2, J17.7, J17.8, J17.11, J17.12, J17.15, J17.16, J17.19, J17.20, J18.11, J18.12, NT2.2, P1.2, P1.4, P2.2, P2.4, Q2.3 (S), R1.2, R2.2, R3.2, R4.2, R11.2, R14.2, R17.1, R21.2, R97.2, TB2.8, TH1.2, TP15.1, U22.4 (~CE), U22.8 (VSS), U22.17 (VSS), U23.6 (V-), U24.2 (GND), U25.2 (GND), U26.2 (IN-), U26.4 (OUT-), U29.2 (GND)
PHONES_L: J9.T, R41.2, TB1.4
PHONES_R: J9.R, R42.2, TB1.5
PWR_GOOD: J18.6, R92.2, TP26.1
SD_CD: A1.29 (IO45), J5.9 (DET), R35.2
SD_CLK: A1.27 (IO43), J5.5 (CLK), TP10.1
SD_CMD: A1.28 (IO44), J5.3 (CMD), R30.2
SD_D0: A1.23 (IO39), J5.7 (DAT0), R31.2
SHDN: Q5.1 (G), R113.2, SW3.1 (A), U46.2 (SHDN)
SPARE_ADC: C100.1, R74.1
SPARE_C: U38.8, U38.9 (-)
SPARE_D: U38.13 (-), U38.14
SPARE_E: U39.13 (-), U39.14
SPARE_F: U45.8, U45.9 (-)
SPARE_G: U45.13 (-), U45.14
SPI2_MISO: A1.39 (IO8), U31.6 (SPI_MISO), U40.12 (Dout)
SPI2_MOSI: A1.38 (IO7), U31.5 (SPI_MOSI), U40.11 (Din)
SPI2_SCK: A1.37 (IO6), U31.4 (SPI_SCK), U40.13 (CLK)
STRAP36: A1.9 (IO36), R24.1
SW5: D5.1 (K), L2.2, U25.1 (SW)
SW12: D4.1 (K), L1.2, U24.1 (SW)
SWBL: D7.1 (K), L4.2, U29.1 (SW)
SW_L_COM: C78.1, U47.10 (COM1)
SW_MIC: C126.2, U47.2 (NO1), U47.4 (NO2)
SW_R_COM: C80.1, U47.6 (COM2)
TEMP_MON: C102.1, R77.1, TH2.2, U40.8 (CH7)
TH: R107.2, R108.1, U46.14 (TH)
TMR: R4.1, U22.14 (TMR)
TS: R5.2, TH1.1
UART0_RX: A1.22 (IO38), J4.3
UART0_TX: A1.21 (IO37), J4.2
USB_DM_C: J1.A7 (D-), J1.B7 (D-), U20.3 (I/O2)
USB_DP_C: J1.A6 (D+), J1.B6 (D+), U20.1 (I/O1)
USB_HS_DM: A1.7 (USB_DM), TP12.1, U20.4 (I/O2)
USB_HS_DP: A1.6 (USB_DP), TP11.1, U20.6 (I/O1)
VBUS_CHG: D1.1 (A1), F1.1, J1.A4 (VBUS), J1.A9 (VBUS), J1.B4 (VBUS), J1.B9 (VBUS), R6.1, TP1.1, U20.5 (VBUS), U22.5 (EN2), U22.6 (EN1)
VBUS_F: C1.1, C2.1, F1.2, R5.1, U22.13 (IN)
VNEG: C59.2, U32.5 (VNEG)
VREF33: C94.1, C95.1, FB6.2, U40.15 (Vref)
VREF_ADC: C72.1, C73.1, U34.1 (VREF)
VSYS: C4.1, C5.1, C10.1, C14.1, J17.1, J17.2, L1.1, L2.1, R12.1, R15.1, TP2.1, U22.10 (OUT), U22.11 (OUT), U24.5 (IN), U25.5 (IN)
XSMT: C65.1, R36.2, U32.17 (XSMT)

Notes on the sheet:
PRE-FREEZE / DO NOT FABRICATE
CORE-2 rev.1 research schematic - ESP32-P4 + ESP32-C6. Do not order boards before P1 benchmark and spec/90 sign-off.
Project files: README.md, pinmap.md, power-tree.md, interfaces.md. GPIO conflicts: 0 (check_pinmap.py).
POWER: USB-C, BQ24074 charge/path, BMS 1S, MT3608 x3 (+12/+5/BL20), MP1584 3V3_MCU, AP2112 x2, MC34063 -12V
MCU: ESP32-P4 module slot, ESP32-C6 Wi-Fi/BLE (SPI esp-hosted), USB-C HS, microSD SDIO
AUDIO: PCM5102A DAC + PCM1808 ADC (I2S), TL072 LINE/PHONES, rear jacks, mic (MAX9814 + line/mic switch + I2S1 MEMS, D-91)
CV: 2x MCP4728 (0x60/0x61), 6x TL074 x4.9, CV IN level shift, MCP3208 + chains
MIDI TRS-A: 6N137 IN / 74HCT125 OUT; GATE drivers 2N7000; LED level shifter
MODULE BUS: 2x IDC-26 analog bus (+-12V, CV1..4, GATE, audio), per-port protection
PANEL-2 + REAR I/O: J14 IDC-26 control, J15 FFC-40 LCD, J16 IDC-16 digital exp, rear jacks TB1/TB2
TEST POINTS (TP1..TP22)
POWER FLAGS (net drivers for ERC)

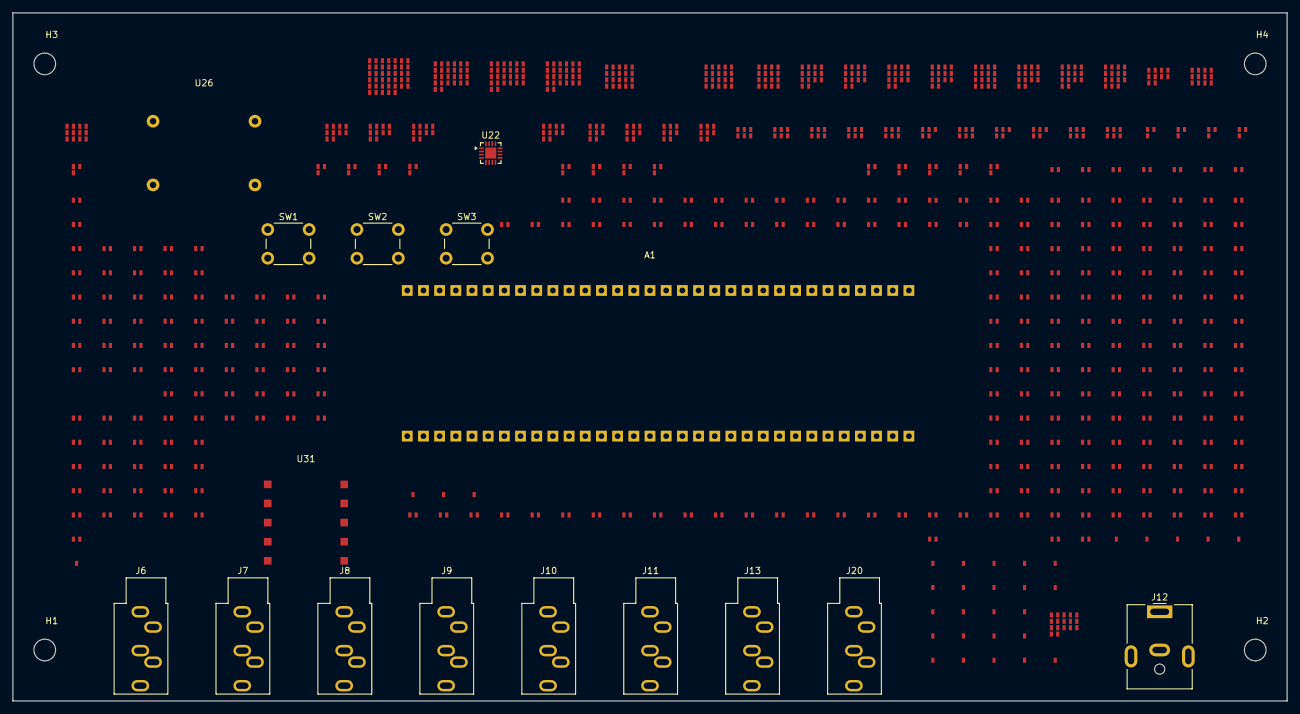
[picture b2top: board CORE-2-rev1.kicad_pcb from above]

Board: 6 copper layers, 200.0 x 108.0 mm, 377 parts (0 on the bottom side), 232 nets, no tracks yet.

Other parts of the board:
H1, H2, H3, H4: MountingHole; MountingHole_M3_3.4mm

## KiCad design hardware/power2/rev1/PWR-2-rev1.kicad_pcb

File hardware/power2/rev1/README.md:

# PWR-2 rev.1 — PCB scaffold (PRE-FREEZE)

> **Не заказывать PCB.** Каркас 90×70 мм из `mechanical/board-fit/`: контур, 4×M2.5,
> keepout-зоны, 4 слоя **2 oz**. Нет посадочных мест/связей/меди.

## Файлы

| Файл | Что |
|---|---|
| `PWR-2-rev1.kicad_pcb` | плата 90×70, 4×M2.5 (Ø2.8, H1–H4), keepout `battery-conn` и `hot-loop`, стек 4 слоя 1.6 мм, медь 2 oz |
| `PWR-2-rev1.svg/.pdf` | контур + шелкография |
| `PWR-2-rev1.drc.rpt` | DRC: **0 нарушений, 0 unconnected** |
| `../core2/rev1/gen_scaffold.py`, `verify_scaffold.py` | генератор/сверка (±0.05 мм) — PASS |

## Параметры

- Контур: 90×70 мм (origin world 145;65), площадь 6 300 мм².
- Крепёж: 4×M2.5 Ø2.8 (NPTH, стойка Ø6).
- Стек: 4 меди (F.Cu/In1/In2/B.Cu), 1.6 мм, **2 oz** (0.07 мм) — силовые 3 А.
- Keepout: `battery-conn` (разъём/предохранитель/шунт у края), `hot-loop` (TPS61088 + индуктивность, тепловой).

## Проверки

- DRC: 0 errors/warnings/unconnected.
- Сверка ±0.05: контур, 4 отверстия, 2 keepout, 4 Cu (2 oz), 1.6 мм — PASS.

## Что дальше

1. Импорт netlist/посадочных мест PWR-2 rev.1 (TPS61088, LMR33630, BQ24074 EVM? — после стенда docs/44).
2. Силовые полигоны 3 А, тепловые vias, J3 (IDC-20 vs Micro-Fit, O-11), звезда PGND.
3. DFM `hardware/power2/dfm.md` + PWR 13/13 (docs/51), затем заказ.

## Нетлист и посадочные места — первый импорт (2026-11-06)

- Источник: `hardware/power2/netlist.xml` + `BOM-power2.csv`.
- **Refs: 128/128**; 4 NPTH-крепления M2.5 — из каркаса.
- **Footprints: 128**; pads **328**; **Placeholder: 0** (все footprint'ы есть в BOM/стандартных
  библиотеках; силовые — проверить thermal pad/2 oz).
- **DRC: 0 errors / 0 warnings; unconnected = 263** — допустимо.
- Зоны: силовая зона (hot-loop/battery-conn) — при ручной разводке; сетка — черновая.
- Перегенерация: `python hardware/core2/rev1/gen_scaffold.py && python hardware/core2/rev1/import_netlist.py`.
- Дальше: трассировка 3 А/тепловые полигоны после PWR 13/13; J3 (IDC vs Micro-Fit).

## Реальные футпринты и DRC-правила (2026-11-06)

- **Placeholder'ы: 0** (все footprint'ы из BOM/KiCad). Footprints 128 (+4 NPTH), pads 332,
  refs 128/128; **DRC 0/0**, unconnected 263.
- **DRC-правила** (`PWR-2-rev1.kicad_pro`): класс `Power` — ширина 1.0 мм (силовые 3 А — при
  разводке до 2 мм/полигоны), via 0.8/0.45; diff pair 0.2/0.2; каркасные silk/courtyard ignore.
- **GND-полигоны (план):** PGND-заливка на F.Cu/B.Cu, звезда у входных ёмкостей; силовая зона
  (hot-loop) — тепловые полигоны/viи; батарейный разъём — отдельный возврат; заливка — после
  PWR 13/13 и трассировки.

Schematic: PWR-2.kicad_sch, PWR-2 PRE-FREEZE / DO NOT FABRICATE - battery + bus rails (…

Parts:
BT1, BT2: 18650 3.6V 3.5Ah; BatteryHolder_Keystone_1042_1x18650
C1, C2, C5, C8, C9, C12, C13, C14, C17, C20, C23, C24, C27, C28, C31, C32, C34, C35, C36, C37, C38, C39, C40: 100n; C_0805_2012Metric
C3, C6, C7, C25, C26: 22uF; C_1210_3225Metric
C4, C15: 1uF; C_0805_2012Metric
C10, C11, C21, C22: 47uF/25V; CP_Elec_6.3x7.7
C16, C18, C19: 22uF/25V; C_1210_3225Metric
C29, C30, C33: 47uF; CP_Elec_6.3x7.7
D1, D2, D5, D6: SMBJ5.0A; D_SMA
D3, D4: SMAJ15A; D_SMA
D7, D8: SS34; D_SMA
F1: 5 A; Fuse_1206_3216Metric
F2: 0.5 A; Fuse_1206_3216Metric
F3: 0.3 A; Fuse_1206_3216Metric
F4: 2 A; Fuse_1206_3216Metric
F5: 2.5 A; Fuse_1206_3216Metric
J1: PACK 3P; TerminalBlock_4Ucon_1x03_P3.50mm_Vertical
J2: SW panel; PinHeader_1x02_P2.54mm_Vertical
J3: J-PWR (IDC-20); IDC-Header_2x10_P2.54mm_Vertical
J4: J-CTRL (IDC-12); IDC-Header_2x06_P2.54mm_Vertical
L1: 10uH / 4A; L_Bourns_SRN6045TA
L2, L6: 4.7uH; L_Bourns_SRN6045TA
L3: 22uH / 2A; L_Bourns_SRN6045TA
L4: 10uH; L_Bourns_SRN6045TA
L5: 10uH / 6A; L_Bourns_SRN6045TA
Q1, Q4, Q5: AO3401A P-FET; SOT-23
Q2, Q3, Q7: AO3400A; SOT-23
Q6: MMBT3904; SOT-23
Q9, Q10: 2N7002; SOT-23
R1, R4, R5, R6, R8, R9, R14, R16, R22, R23, R25, R27, R29, R36, R37, R39: 100k; R_0603_1608Metric
R2, R33, R34, R35, R38: 100R; R_0603_1608Metric
R3, R13, R21, R28, R32: 1k; R_0603_1608Metric
R7, R20: 10k; R_0603_1608Metric
R10: 10R; R_0603_1608Metric
R11, R12: 22R; R_0603_1608Metric
R15: 11k; R_0603_1608Metric
R17, R24: 4.7k; R_0603_1608Metric
R19: 110k; R_0603_1608Metric
R26: 30.9k; R_0603_1608Metric
SW1: POWER OFF/ON
TH1: NTC 10k B3950
TP1: BATT_CELL_P; TestPoint_Pad_D1.5mm
TP2: VBAT; TestPoint_Pad_D1.5mm
TP3: VSYS_SW; TestPoint_Pad_D1.5mm
TP4: 12V_BUS; TestPoint_Pad_D1.5mm
TP5: N12_BUS; TestPoint_Pad_D1.5mm
TP6: 5V_BUS; TestPoint_Pad_D1.5mm
TP7: LED_RET; TestPoint_Pad_D1.5mm
TP8: PWR_GOOD; TestPoint_Pad_D1.5mm
TP9: PGND; TestPoint_Pad_D1.5mm
U1: BQ297xy; SOT-23-6
U2: MAX17048; SOT-23-6
U3, U6: TPS61088; QFN-20-1EP_3x3mm_P0.4mm_EP1.65x1.65mm
U4: LMR33630; SOIC-8_3.9x4.9mm_P1.27mm
U5: PC817; DIP-4_W7.62mm
U7: MCP130-270; SOT-23

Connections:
5V_BUS: C32.1, D5.1 (A1), F4.2, F5.1, J3.13, J3.14, R28.1, TP6.1
5V_F: C29.1, C30.1, C31.1, F4.1, L6.2
5V_LED: C33.1, C34.1, D6.1 (A1), F5.2, J3.17, R32.1
5V_SW: L6.1, R25.1, U6.10 (VOUT), U6.11 (VOUT)
12V_BUS: C13.1, D3.1 (A1), D7.1 (K), J3.5, J3.6, R17.1, TP4.1
12V_F: C10.1, C11.1, C12.1, F2.1, L2.2
12V_OG: D7.2 (A), F2.2
12V_SW: L2.1, R14.1, U3.10 (VOUT), U3.11 (VOUT)
BATT_BM: BT1.2 (-), BT2.2 (-), C1.2, D1.2 (A2), J1.2, Q1.1 (G), Q2.3 (D), R1.2, TH1.2, U1.4 (VSS)
BATT_CELL_P: BT1.1 (+), BT2.1 (+), F1.1, J1.1, R10.1, R13.1, TP1.1
BATT_MON: J4.1, R13.2
BMS_BAT: C1.1, R2.2, U1.5 (BAT)
BMS_MID: Q2.2 (S), Q3.2 (S), R4.2, R5.2
BOOT_N12: C14.1, U4.7 (BOOT)
CS_BMS: R3.1, U1.6 (V-)
EN5_IC: C38.1, Q10.3 (D), R27.2, U6.2 (EN)
EN12_IC: C35.1, Q9.3 (D), R16.2, U3.2 (EN)
EN_5V: C40.1, Q10.1 (G), R38.2, R39.1
EN_5V_C: J4.10, R38.1
EN_BUS12: Q9.1 (G), R33.2, R36.1
EN_BUS12_C: J4.7, R33.1
EN_LED5: C37.1, Q7.1 (G), R35.2, R37.1
EN_LED5_C: J4.9, R35.1
EN_N12: C36.1, R21.1, R22.1, R34.2
EN_N12_C: J4.8, R34.1
EN_N12_IC: C20.1, R23.1, U4.3 (EN), U5.4
FB_5: R25.2, R26.1, U6.4 (FB)
FB_12: R14.2, R15.1, U3.4 (FB)
FB_N12: R19.2, R20.1, U4.5 (FB)
FUEL_ALRT: J4.5, U2.5 (ALRT)
FUEL_SCL: R12.1, U2.4 (SCL)
FUEL_SCL_C: J4.4, R12.2
FUEL_SDA: R11.1, U2.3 (SDA)
FUEL_SDA_C: J4.3, R11.2
G_CHG: Q3.1 (G), R5.1, U1.2 (Cout)
G_DIS: Q2.1 (G), R4.1, U1.3 (Dout)
G_MASTER: C2.1, Q4.1 (G), Q5.1 (G), Q6.2 (C), R6.2
LED_RET: C39.1, J3.18, Q7.3 (D), R29.1, TP7.1
MASTER_SW: J2.2, R7.1, R9.1, SW1.2 (B)
N12_BUS: C24.2, D4.2 (A2), D8.2 (A), J3.9, J3.10, R24.1, TP5.1
N12_F: C21.2, C22.2, C23.2, F3.1, L4.2
N12_OG: D8.1 (K), F3.2
N12_SW: C15.2, C16.2, C17.2, C18.2, C19.2, C20.2, L4.1, R20.2, U4.1 (GND), U4.9 (GND), U5.3
NTC_PACK: J1.3, J4.2, TH1.1
OPT_ANODE: R21.2, U5.1
PACK_F: D1.1 (A1), F1.2, Q1.3 (D)
PGND: C3.2, C4.2, C5.2, C6.2, C7.2, C8.2, C9.2, C10.2, C11.2, C12.2, C13.2, C18.1, C19.1, C21.1, C22.1, C23.1, C24.1, C25.2, C26.2, C27.2, C28.2, C29.2, C30.2, C31.2, C32.2, C33.2, C34.2, C35.2, C36.2, C37.2, C38.2, C39.2, C40.2, D2.2 (A2), D3.2 (A2), D4.1 (A1), D5.2 (A2), D6.2 (A2), J3.7, J3.8, J3.11, J3.12, J3.15, J3.16, J3.19, J3.20, J4.11, J4.12, L3.2, Q3.3 (D), Q6.3 (E), Q7.2 (S), Q9.2 (S), Q10.2 (S), R3.2, R8.2, R9.2, R15.2, R17.2, R19.1, R22.2, R24.2, R26.2, R28.2, R29.2, R32.2, R36.2, R37.2, R39.2, TP9.1, U2.2 (GND), U2.6 (QSTRT), U3.5 (MODE), U3.6 (GND), U3.7 (PGND), U3.12 (AGND), U3.13 (EP), U5.2, U6.5 (MODE), U6.6 (GND), U6.7 (PGND), U6.12 (AGND), U6.13 (EP), U7.3 (VSS)
PWR_GOOD: J4.6, TP8.1, U7.1 (~RST)
Q6_B: Q6.1 (B), R7.2, R8.1
SS_5: C28.1, U6.3 (SS)
SS_12: C9.1, U3.3 (SS)
SW_5: L5.2, U6.8 (SW), U6.9 (SW)
SW_12: L1.2, U3.8 (SW), U3.9 (SW)
SW_N12: C14.2, L3.1, U4.8 (SW)
VBAT: J3.3, J3.4, Q1.2 (S), R1.1, R2.1, TP2.1
VCC_N12: C15.1, U4.6 (VCC)
VGAUGE: C4.1, C5.1, R10.2, U2.1 (VDD)
VSYS: C2.2, J2.1, J3.1, J3.2, Q4.2 (S), R6.1, SW1.1 (A)
VSYS_MID: Q4.3 (D), Q5.2 (S)
VSYS_SW: C3.1, C6.1, C7.1, C8.1, C16.1, C17.1, C25.1, C26.1, C27.1, D2.1 (A1), L1.1, L5.1, Q5.3 (D), R16.1, R23.2, R27.1, TP3.1, U3.1 (VIN), U4.2 (VIN), U6.1 (VIN), U7.2 (VDD)

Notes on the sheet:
PRE-FREEZE / DO NOT FABRICATE
PWR-2 rev.1 research schematic - 1S2P 18650 + BMS + MAX17048 + TPS61088/+12 V + LMR33630 IBB/-12 V + TPS61088/+5 V.
Charger/power-path (BQ24074) stays on CORE-2: PWR-2 converters are fed ONLY by VSYS (BQ24074 OUT). No MC34063, no charge pump.
Docs: README.md, power-tree-pwr2.md, interfaces.md, docs/schema/pwr2.md
PACK 1S2P: 2x18650 parallel, J1 pack, F1 5 A, Q1 reverse-FET, D1 TVS, TH1 NTC
BMS 1S: BQ297xy + 2x AO3400A (common source), OVP/UVP/OCP/SCP; VBAT = P+ -> BQ24074 BAT
MASTER LOAD SWITCH: back-to-back AO3401A, MMBT3904 high-side driver, panel switch J2/SW1, TVS
FUEL GAUGE MAX17048 (I2C 0x36) + Kelvin sense at the cell + analog backup BATT_MON
BUS +12 V: TPS61088 sync boost 12.15 V -> C-L-C pi-filter -> polyfuse 0.5 A -> TVS (budget 330 mA)
BUS -12 V: LMR33630 IBB (GND МС = -12 V, VIN = VSYS+12 V) + opto EN -> pi-filter -> polyfuse 0.3 A (budget 95 mA)
LOGIC/AUDIO +5 V: TPS61088 sync boost 5.10 V -> pi-filter -> polyfuse 2 A (budget 1.0 A)
LED BRANCH: polyfuse 2.5 A + AO3400A low-side switch on the LED return (EN_LED5, OFF by default)
SUPERVISOR + EN INPUTS: MCP130-270 (PWR_GOOD open-drain), 100R/100n EN filters (3.3 V-safe)
INTERFACE: J3 IDC-20 (VSYS/VBAT/+12/-12/+5/5V_LED/LED_RET/pairs), J4 IDC-12 (sense/I2C/status/EN)
TEST POINTS TP1..TP9
POWER FLAGS (net drivers for ERC)
